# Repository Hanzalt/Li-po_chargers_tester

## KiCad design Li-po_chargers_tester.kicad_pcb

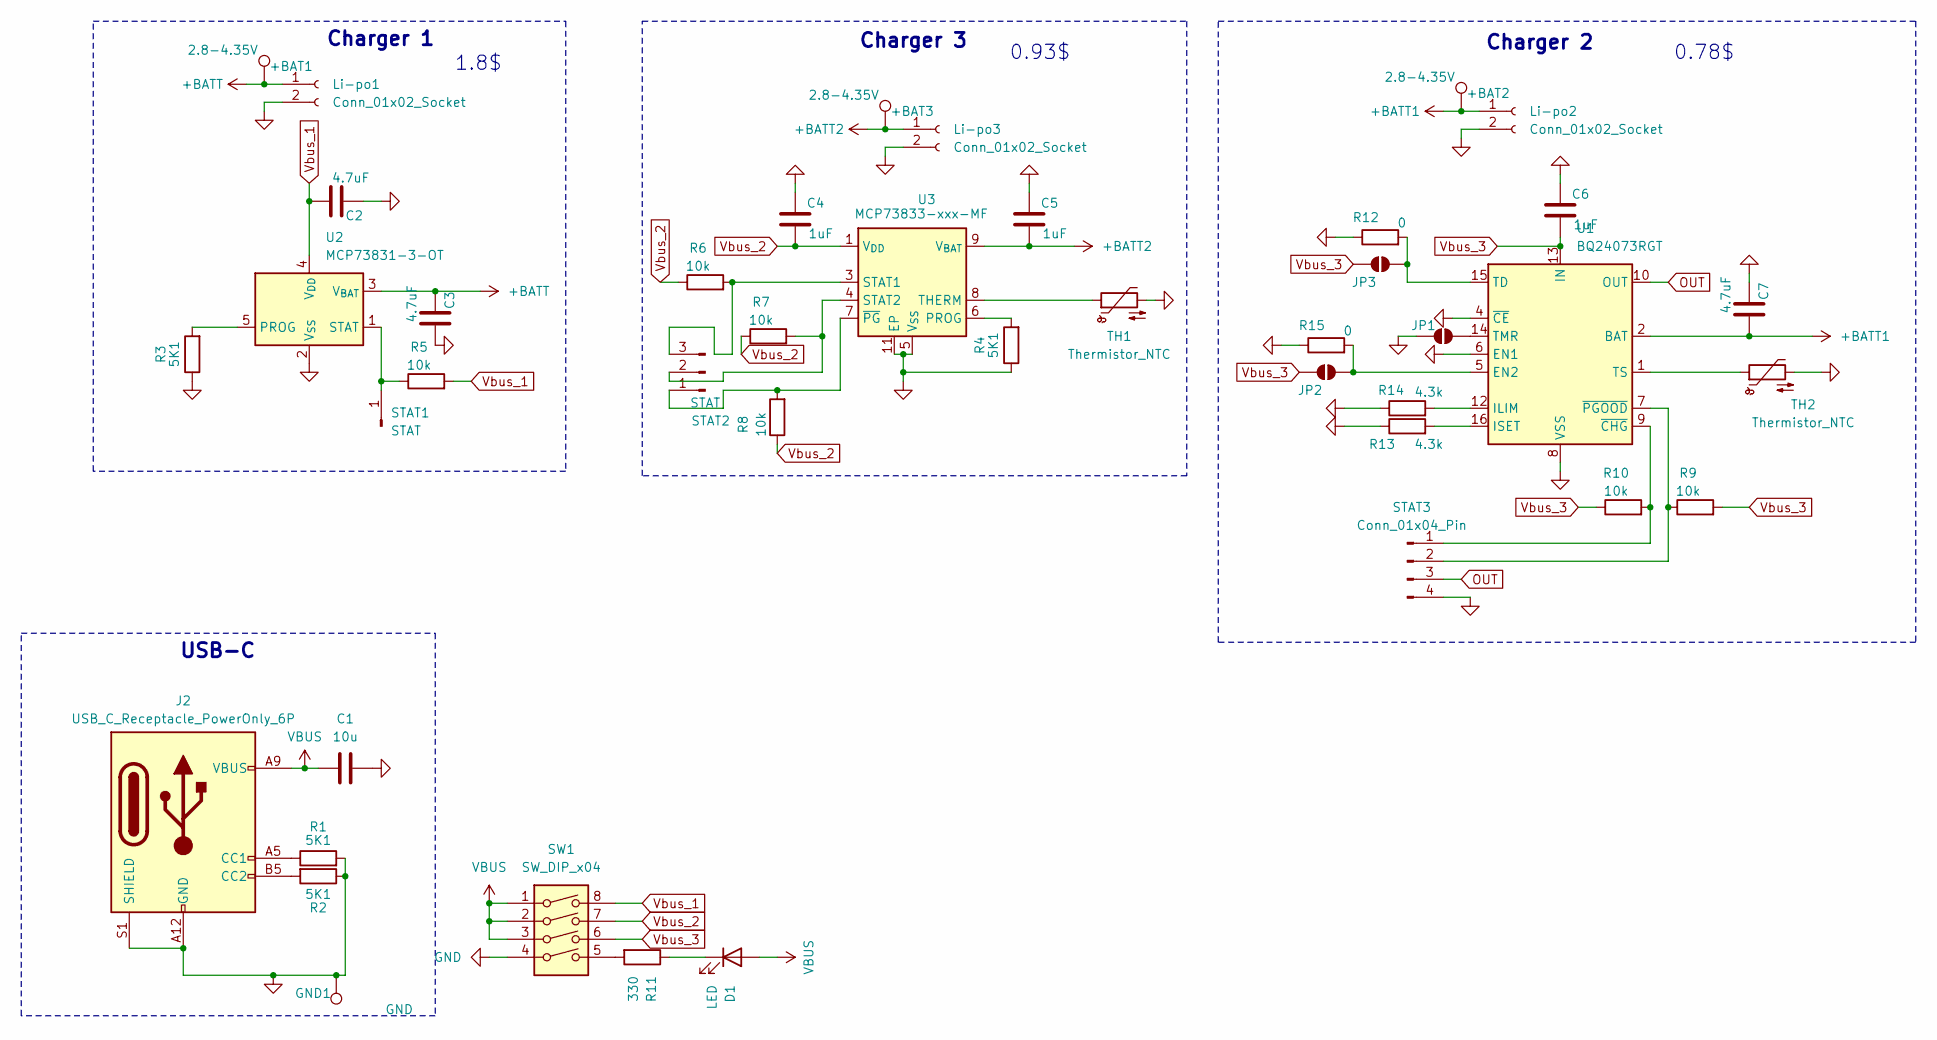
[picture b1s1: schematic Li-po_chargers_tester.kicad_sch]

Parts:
+BAT1, +BAT2, +BAT3: 2.8-4.35V; TestPoint_Pad_D1.5mm
C1: 10u; C_0603_1608Metric; LCSC C77040
C2, C3, C7: 4.7uF; C_0603_1608Metric; LCSC C1705
C4, C5, C6: 1uF; C_0603_1608Metric; LCSC C15849
D1: LED; LED_0603_1608Metric; LCSC C2286 Copy
GND1: GND; TestPoint_Pad_D1.5mm
J2: USB_C_Receptacle_PowerOnly_6P; USB_C_Receptacle_GCT_USB4135-GF-A_6P_TopMnt_Horizontal; LCSC C2927283
JP1, JP2, JP3: SolderJumper_2_Open; SolderJumper-2_P1.3mm_Open_RoundedPad1.0x1.5mm
Li-po1, Li-po2, Li-po3: Conn_01x02_Socket; JST_SUR_SM02B-SURS-TF_1x02-1MP_P0.80mm_Horizontal; LCSC C566239
R1, R2, R3, R4: 5K1; R_0402_1005Metric; LCSC C25905
R5, R6, R7, R8, R9, R10: 10k; R_0603_1608Metric; LCSC C25804
R11: 330; R_0603_1608Metric; LCSC C23138
R12, R15: 0; R_0805_2012Metric; LCSC C17477
R13, R14: 4.3k; R_0402_1005Metric; LCSC C25899
STAT1: STAT; PinSocket_1x01_P2.54mm_Vertical
STAT2: STAT; PinSocket_1x03_P2.54mm_Vertical
STAT3: Conn_01x04_Pin; PinSocket_1x04_P2.54mm_Vertical
SW1: SW_DIP_x04; SW_DIP_SPSTx04_Slide_9.78x12.34mm_W7.62mm_P2.54mm
TH1, TH2: Thermistor_NTC; R_0402_1005Metric; LCSC C333993
U1: BQ24073RGT; VQFN-16-1EP_3x3mm_P0.5mm_EP1.6x1.6mm; LCSC C15220
U2: MCP73831-3-OT; SOT-23-5; LCSC C625598
U3: MCP73833-xxx-MF; DFN-10-1EP_3x3mm_P0.5mm_EP1.58x2.35mm; LCSC C623859

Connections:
+BATT: +BAT1.1, C3.2, Li-po1.1, U2.3 (V_{BAT})
+BATT1: +BAT2.1, C7.1, Li-po2.1, U1.2 (BAT), U1.3 (BAT)
+BATT2: +BAT3.1, C5.2, Li-po3.1, U3.9 (V_{BAT}), U3.10 (V_{BAT})
GND: C1.2, C2.2, C3.1, C4.1, C5.1, C6.1, C7.2, GND1.1, J2.A12 (GND), J2.B12 (GND), J2.S1 (SHIELD), JP1.1 (A), Li-po1.2, Li-po2.2, Li-po3.2, R1.2, R2.1, R3.1, R4.1, R12.1, R13.1, R14.1, R15.1, STAT3.4, SW1.4, TH1.2, TH2.2, U1.4 (~CE), U1.6 (EN1), U1.8 (VSS), U1.17 (VSS), U2.2 (V_{SS}), U3.5 (V_{SS}), U3.11 (EP)
unnamed: D1.1 (K), R11.1
unnamed: J2.A5 (CC1), R1.1
unnamed: J2.B5 (CC2), R2.2
unnamed: JP1.2 (B), U1.14 (TMR)
unnamed: JP2.2 (B), R15.2, U1.5 (EN2)
unnamed: JP3.2 (B), R12.2, U1.15 (TD)
unnamed: R11.2, SW1.5
unnamed: R5.1, STAT1.1, U2.1 (STAT)
unnamed: R8.2, STAT2.1, U3.7 (~PG)
unnamed: R7.2, STAT2.2, U3.4 (STAT2)
unnamed: R6.2, STAT2.3, U3.3 (STAT1)
unnamed: R10.2, STAT3.1, U1.9 (~CHG)
unnamed: R9.1, STAT3.2, U1.7 (~PGOOD)
unnamed: R14.2, U1.12 (ILIM)
unnamed: R13.2, U1.16 (ISET)
unnamed: TH2.1, U1.1 (TS)
unnamed: R3.2, U2.5 (PROG)
unnamed: R4.2, U3.6 (PROG)
unnamed: TH1.1, U3.8 (THERM)
OUT: STAT3.3, U1.10 (OUT), U1.11 (OUT)
VBUS: C1.1, D1.2 (A), J2.A9 (VBUS), J2.B9 (VBUS), SW1.1, SW1.2, SW1.3
Vbus_1: C2.1, R5.2, SW1.8, U2.4 (V_{DD})
Vbus_2: C4.2, R6.1, R7.1, R8.1, SW1.7, U3.1 (V_{DD}), U3.2 (V_{DD})
Vbus_3: C6.2, JP2.1 (A), JP3.1 (A), R9.2, R10.1, SW1.6, U1.13 (IN)

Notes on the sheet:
USB-C
0.93$
1.8$
0.78$
Charger 2
Charger 1
Charger 3

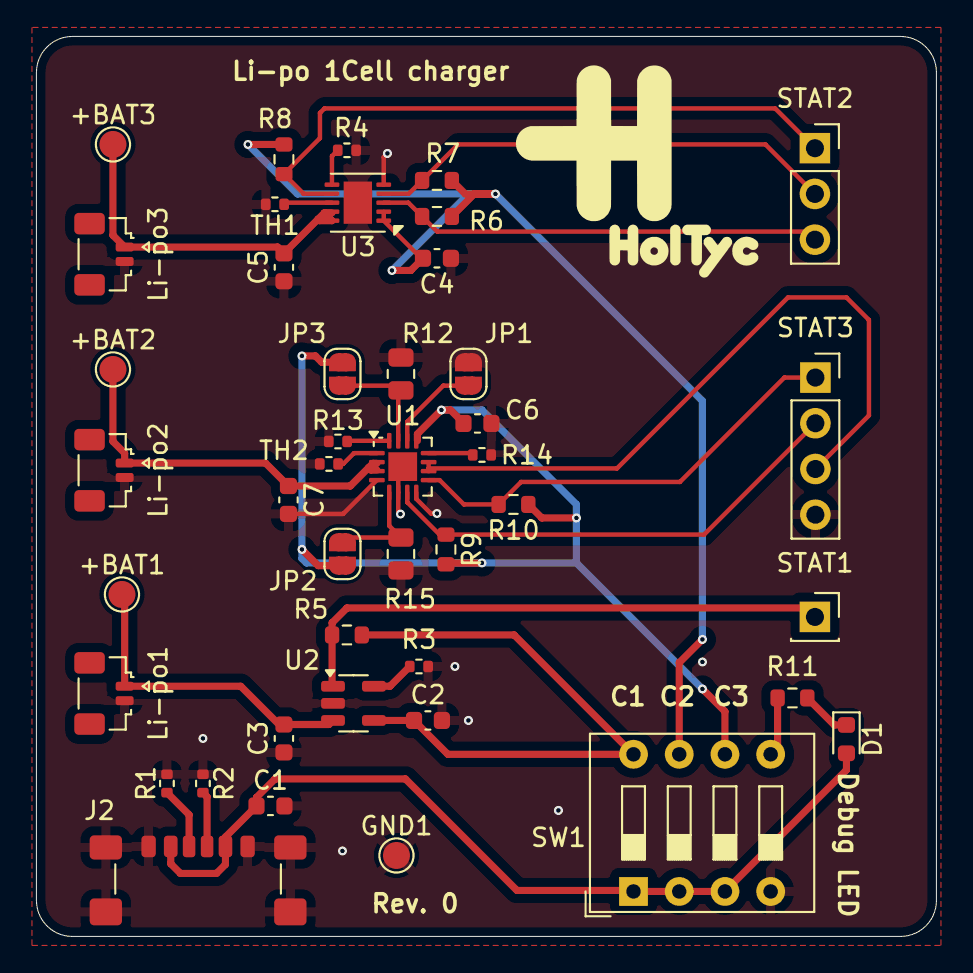
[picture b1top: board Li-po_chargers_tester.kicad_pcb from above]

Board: 2 copper layers, 50.0 x 50.0 mm, 43 parts (0 on the bottom side), 28 nets.

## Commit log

2024-10-13 Init
2024-10-14 Board making #1 I made the whole PCB board. Just minor bug repairment and then it should be good
